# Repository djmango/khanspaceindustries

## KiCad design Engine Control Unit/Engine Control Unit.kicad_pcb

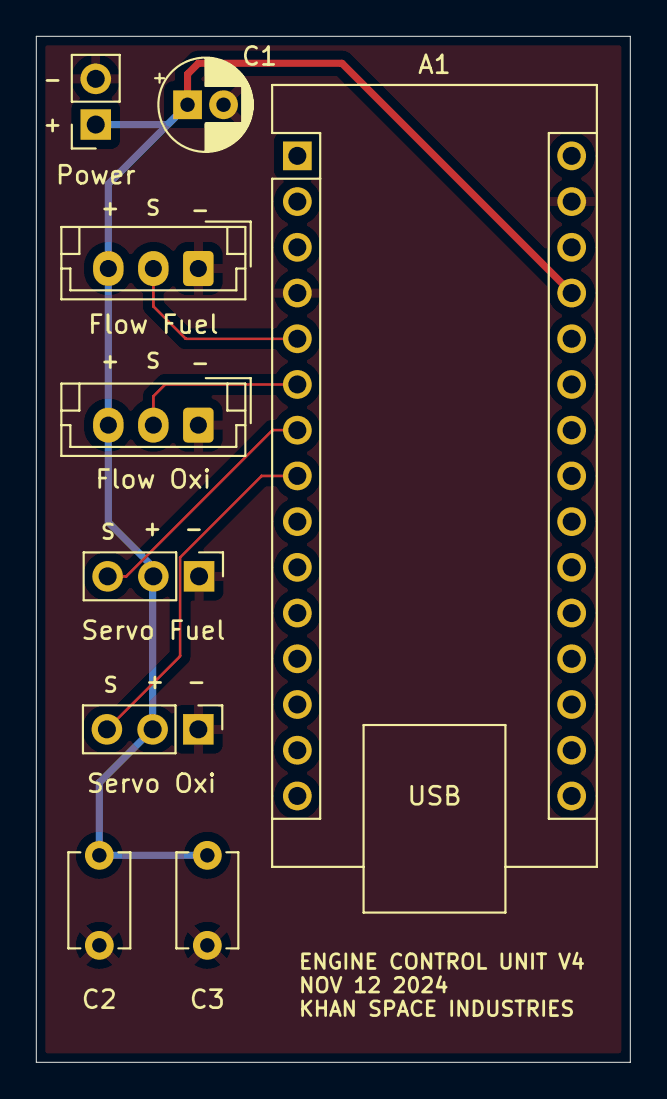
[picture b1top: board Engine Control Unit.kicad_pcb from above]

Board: 2 copper layers, 33.0 x 57.0 mm, 9 parts (0 on the bottom side), 6 nets.

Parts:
A1: Arduino_Nano_v3.x; Arduino_Nano
C1: 10n C_Polarized; CP_Radial_D5.0mm_P2.00mm
C2, C3: 100n; C_Disc_D5.1mm_W3.2mm_P5.00mm
Flow Fuel: Conn_01x03_Pin; JST_EH_B3B-EH-A_1x03_P2.50mm_Vertical
Flow Oxi: Conn_01x03_Pin; JST_EH_B3B-EH-A_1x03_P2.50mm_Vertical
Power: Conn_01x02_Socket; PinSocket_1x02_P2.54mm_Vertical
Servo Fuel: Conn_01x03_Pin; PinHeader_1x03_P2.54mm_Vertical
Servo Oxi: Conn_01x03_Pin; PinHeader_1x03_P2.54mm_Vertical

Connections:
+5V: A1.27 (+5V), C1.1, C2.2, C3.2, Flow Fuel.3, Flow Oxi.3, Power.1, Servo Fuel.2, Servo Oxi.2
GND: A1.4 (GND), A1.29 (GND), C1.2, C2.1, C3.1, Flow Fuel.1, Flow Oxi.1, Power.2, Servo Fuel.1, Servo Oxi.1
unnamed: A1.5 (D2), Flow Fuel.2
unnamed: A1.6 (D3), Flow Oxi.2
unnamed: A1.7 (D4), Servo Fuel.3
unnamed: A1.8 (D5), Servo Oxi.3

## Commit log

2024-10-03 :rocket: (Init) First version of khan heavy space site :)
    i did not sleep
2024-10-18 :rocket: (Vision) Publish vision writeup + october wip update
2024-11-02 :bug: (Mobile) Fix khan space industries header on mobile
2024-11-02 :sparkles: (Updates) Add nov start updates
2024-11-06 :sparkles: (Flowrate) Wrote flow rate calc software + basic graphing suite
2024-11-07 :sparkles: (PCB) Add PCBs and refactor to ground control suite
2024-11-07 :fire: (Prune) Prune old files
2024-11-07 :pencil: (Landing Page) Update landing page content
2024-11-07 :wrench: (Landing Page) Update landing page title
2024-11-09 :sparkles: (Ground Control) Started new ground control suite, arduino code ready for testing
    Now outputs a csv of data and expects constant serial communication about valve position, defaults to emergency closed
2024-11-10 :sparkles: (Arduino) Add independent control for fuel/oxi servos and minor code improvements
2024-11-10 :sparkles: (Ground Control) Basic two-way comms for ground control works with plotting
    Little slow at the moment and laggy, not optimzied fixing now. buttons work tho :)
2024-11-10 :zap: (GUI) Optimize GUI perf of ground control system
    much faster and more oganized
2024-11-10 :sparkles: (GUI) Add graphs for servo pos and emergency and minor perf imporvements
2024-11-11 :sparkles: (Ground Control) Added logging and minor gui improvements
2024-11-11 :sparkles: (Lab Assistant) Add basic lab assistant to write experiment notes from vids of procedure
2024-11-13 :bug: (Pins) Change pins to interupt
2024-12-10 :sparkles: (Landing) v1 hotfire and %s to website
